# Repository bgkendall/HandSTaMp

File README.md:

# ~~HandSTaMp~~ HandCHime

## Bill of Materials

| Reference | Silkscreen | Part                        | Footprint | Purpose                                        |
|-----------|------------|-----------------------------|-----------|------------------------------------------------|
| C1        | µ          | 4.7µF ceramic capacitor     | 0603      | Bulk decoupling capacitor for U1               |
| C2        | n          | 100nF ceramic capacitor     | 0603      | Decoupling capacitor for U1                    |
| D1        | D1         | PMEG2010EA Schottky diode   | SOD-323   | Reverse current protection                     |
| D2, D3    | D2, D3     | 2 × 1N4148 diodes           | SOD-123   | Matrix diodes for SW1/SW2                      |
| F1        | F          | 500mA fuse                  | 0603      | Current overload protection                    |
| J1        | J1         | HRO TYPE-C-31-M-12 USB port |           | For the pluggings in of USB cables             |
| R1, R2    | 1, 2       | 2 × 5.1kΩ resistors         | 0603      | USB power negotiation (Rd) resistors           |
| R3        | 3          | 5.1kΩ resistor              | 0603      | Boot circuit resistor                          |
| S1, S2    | *None*     | 2 × MX-compatible switches  | MX plate¹ | Keys for row 0, columns 0/1; mountings for PCB |
| S3        | *None*     | B3U-1000P                   |           | Boot switch                                    |
| U1        | *None*²    | CH32X035G8U6                | WQFN-28   | ~~Braaaains!~~ Microcontroller                 |
| U2        | U2         | PRTR5V0U2X                  | SOT-143   | ESD protection                                 |

##### Notes

 1. Three-pin “plate-mount” switches can be used as-is. To use five-pin “PCB-mount” switches,
    one of the plastic alignment “pins” must be removed from opposite sides of each switch.
 2. U1 is positioned in the ~4×4mm area in the lower centre of the PCB.

## Debug Interface

The Serial Debug Interface (SDI) pins are assigned as follows:

 1. **S**quare Pin — **S**WDIO
 2. **C**ircular Pin — SW**C**LK

These pins are intended to be small enough to friction fit debug probe wires.
The pins can alternatively be used as the following extra GPIO pins:

 1. Square Pin — PC18
 2. Circular Pin — PC19

Note that these pins are underneath a switch and can only be soldered from the bottom.
Wires should be trimmed as close to the board as possible.

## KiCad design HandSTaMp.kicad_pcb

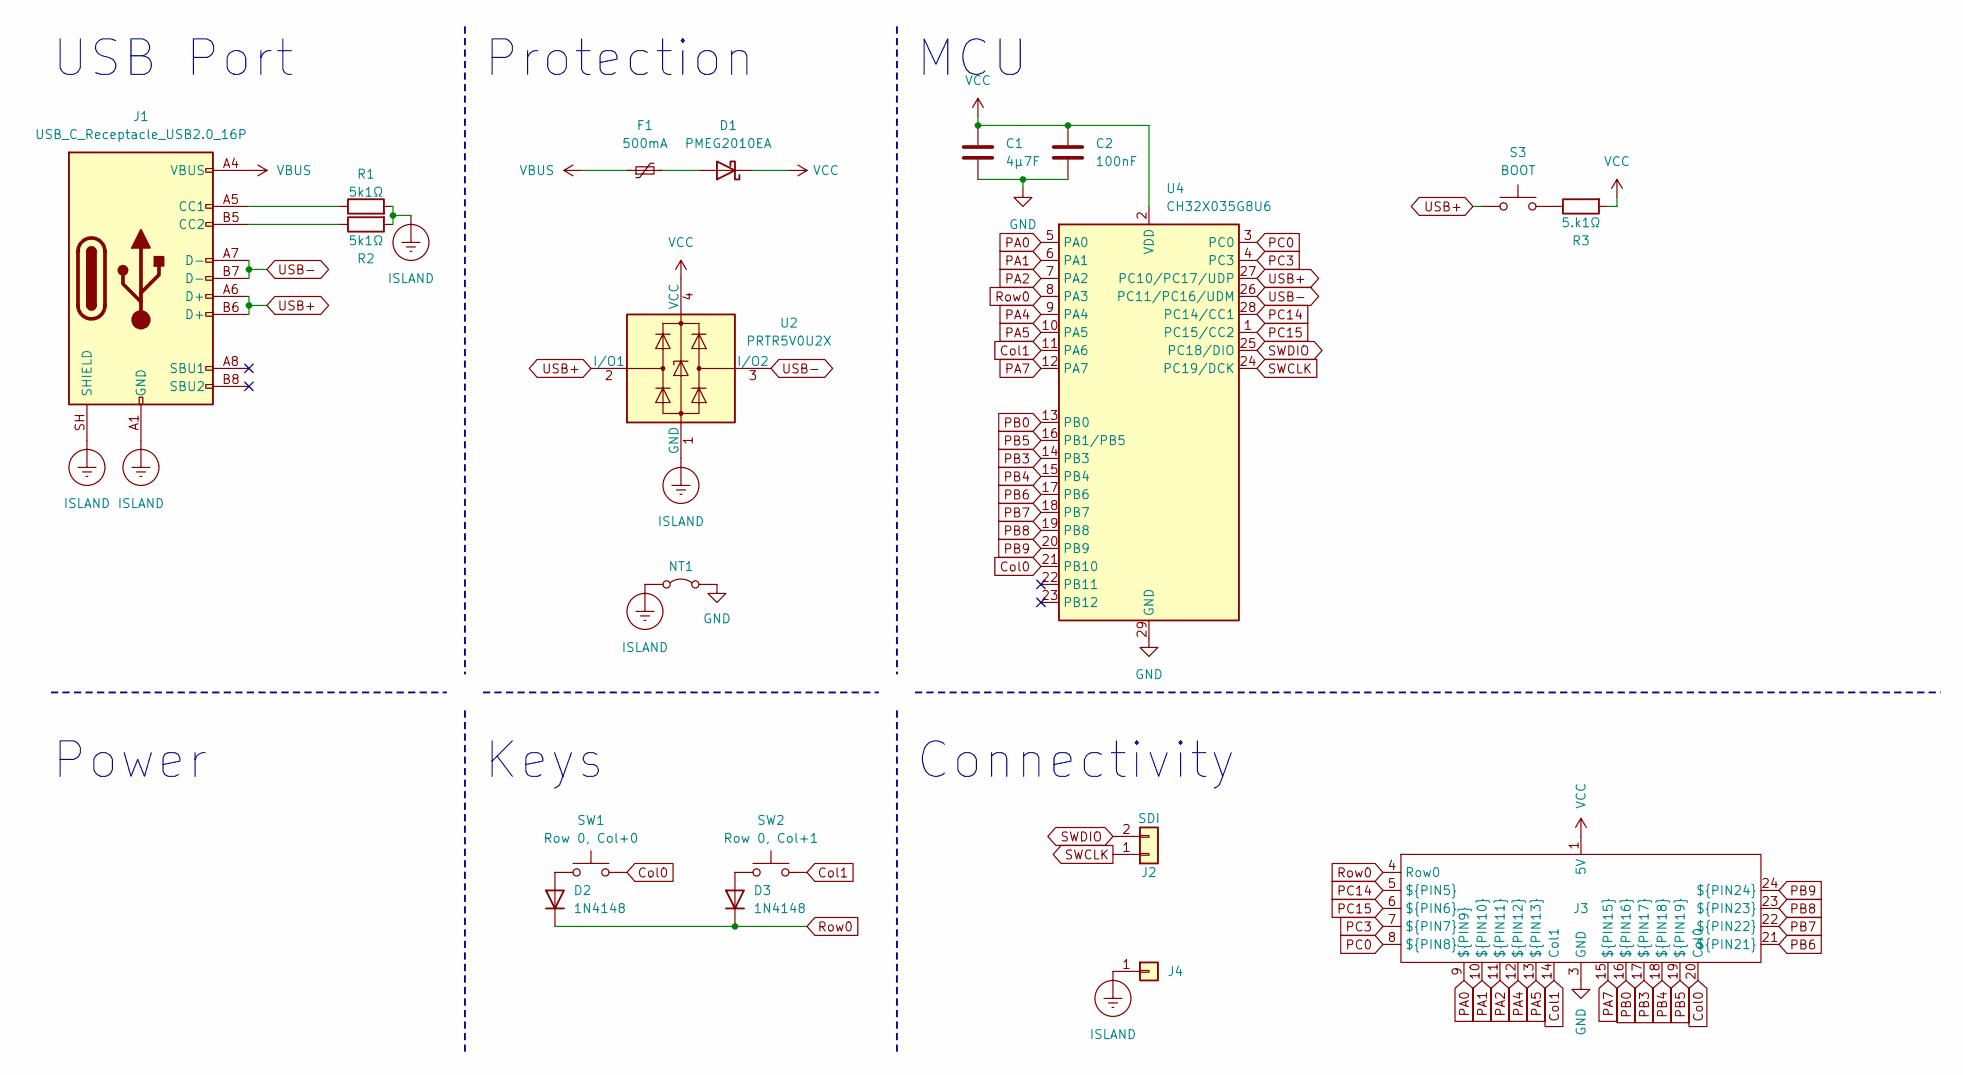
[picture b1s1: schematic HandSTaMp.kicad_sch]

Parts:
C1: 4µ7F; C_0603_1608Metric; MPN CL10A475KO8NNNC; DigiKey 1276-1784-1
C2: 100nF; C_0603_1608Metric; MPN CL10B104KO8NNNC; DigiKey 1276-1005-1
D1: PMEG2010EA; D_SOD-323; MPN PMEG2010EA,115; LCSC C193668
D2, D3: 1N4148; D_SOD-123; MPN 1N4148W; DigiKey 1N4148WQ-7-FDI
F1: 500mA; Fuse_0603_1608Metric; MPN MF-FSMF050X-2; LCSC C210357
J1: USB_C_Receptacle_USB2.0_16P; USB_C_Receptacle_HRO_TYPE-C-31-M-12; MPN TYPE-C-31-M-12; DigiKey 2223-UJ20-C-H-G-SMT-1A-P16 (untested; m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
J2: SDI; SWD
J3: Pins; HandSTaMp
J4: ⏚; SolderWire_1x01_D1mm_OD1.7mm
NT1: Mounting Hole/Isolated Ground Jumper; NetTie-2_SMD_Pad0.5mm
R1, R2: 5k1Ω; R_0603_1608Metric; MPN 0603WAF5101T5E/RC0603FR-075K1L; LCSC C23186
R3: 5.k1Ω; R_0603_1608Metric; MPN 0603WAF3300T5E/RC0603FR-07330RL; LCSC C23138
S3: BOOT; SW_SPST_B3U-1000P; MPN B3U-1000P; LCSC C231329
SW1: Row 0, Col+0; SW_MX_1u_1pinL
SW2: Row 0, Col+1; SW_MX_1u_1pinR
U2: PRTR5V0U2X; SOT-143; MPN PRTR5V0U2X,215; LCSC C12333
U4: CH32X035G8U6; WQFN-28-1EP_4x4mm_P0.4mm_EP2.7x2.7mm

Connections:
Col0: J3.20 (Col0), SW1.1, U4.21 (PB10)
Col1: J3.14 (Col1), SW2.1, U4.11 (PA6)
GND: C1.2, C2.2, J3.3 (GND), NT1.2 (B), U4.29 (GND)
ISLAND: J1.A1 (GND), J1.A12 (GND), J1.B1 (GND), J1.B12 (GND), J1.SH (SHIELD), J4.1 (Pin_1_1), NT1.1 (A), R1.2, R2.2, U2.1 (GND)
unnamed: D1.2 (A), F1.2
unnamed: D2.2 (A), SW1.2
unnamed: D3.2 (A), SW2.2
unnamed: J1.A5 (CC1), R1.1
unnamed: J1.B5 (CC2), R2.1
unnamed: R3.1, S3.2
PA0: J3.9 (${PIN9}), U4.5 (PA0)
PA1: J3.10 (${PIN10}), U4.6 (PA1)
PA2: J3.11 (${PIN11}), U4.7 (PA2)
PA4: J3.12 (${PIN12}), U4.9 (PA4)
PA5: J3.13 (${PIN13}), U4.10 (PA5)
PA7: J3.15 (${PIN15}), U4.12 (PA7)
PB0: J3.16 (${PIN16}), U4.13 (PB0)
PB3: J3.17 (${PIN17}), U4.14 (PB3)
PB4: J3.18 (${PIN18}), U4.15 (PB4)
PB5: J3.19 (${PIN19}), U4.16 (PB1/PB5)
PB6: J3.21 (${PIN21}), U4.17 (PB6)
PB7: J3.22 (${PIN22}), U4.18 (PB7)
PB8: J3.23 (${PIN23}), U4.19 (PB8)
PB9: J3.24 (${PIN24}), U4.20 (PB9)
PC0: J3.8 (${PIN8}), U4.3 (PC0)
PC3: J3.7 (${PIN7}), U4.4 (PC3)
PC14: J3.5 (${PIN5}), U4.28 (PC14/CC1)
PC15: J3.6 (${PIN6}), U4.1 (PC15/CC2)
Row0: D2.1 (K), D3.1 (K), J3.4 (Row0), U4.8 (PA3)
SWCLK: J2.1, U4.24 (PC19/DCK)
SWDIO: J2.2, U4.25 (PC18/DIO)
USB+: J1.A6 (D+), J1.B6 (D+), S3.1, U2.2 (I/O1), U4.27 (PC10/PC17/UDP)
USB-: J1.A7 (D-), J1.B7 (D-), U2.3 (I/O2), U4.26 (PC11/PC16/UDM)
VBUS: F1.1, J1.A4 (VBUS), J1.A9 (VBUS), J1.B4 (VBUS), J1.B9 (VBUS)
VCC: C1.1, C2.1, D1.1 (K), J3.1 (5V), R3.2, U2.4 (VCC), U4.2 (VDD)

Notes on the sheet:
Keys
MCU
Connectivity
Protection
Power
USB Port

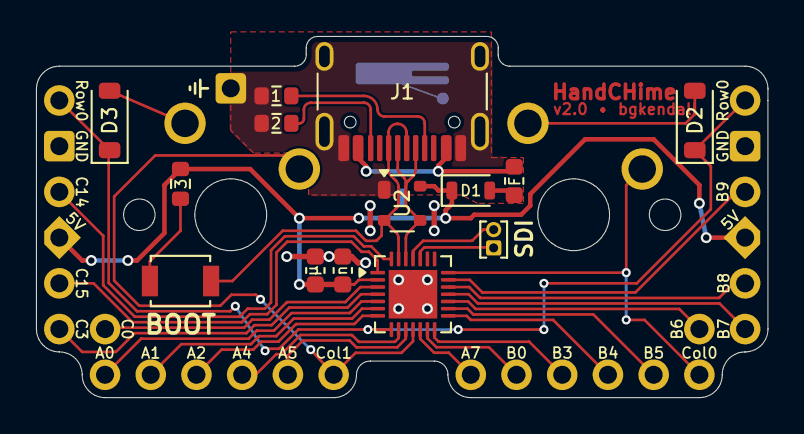
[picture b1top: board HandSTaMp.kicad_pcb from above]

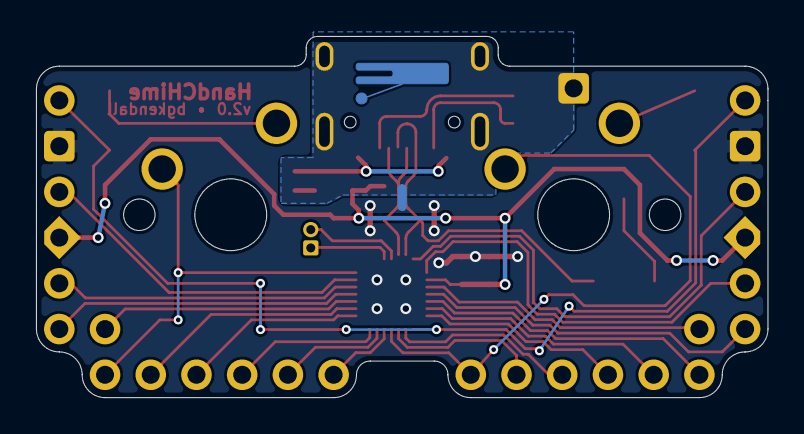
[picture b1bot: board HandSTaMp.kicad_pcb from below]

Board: 2 copper layers, 40.6 x 20.1 mm, 19 parts (3 on the bottom side), 35 nets.

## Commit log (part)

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2026-04-14 Fix README notes
2026-04-14 Tweak routing, especially R1 and C0
2026-04-14 Update constraints and fix various DRC errors
    The logo was getting a “copper slither” warning on the logo, so the handle and base shapes have been merged into one shape.
    The SWD pins have been spaced out a little.
2026-04-24 Refine logo
2026-04-24 Rework LDO area
2026-04-24 Swap column pins to edge of group
2026-04-24 Move version/author label away from D2 silkscreen
2026-04-24 Minor tweaks
2026-04-25 Add LSCC, DigiKey and manufacturer’s part numbers
    BOM could be optimised to substitute some passive components with equivalent “Basic” parts if using JLC assembly.
2026-04-25 Move extra pin to short side
    This better avoids the switch as the left and right sides taper in a bit compared to the top and bottom sides, which are more straight.
2026-04-25 Add pad for PC15 access
2026-04-25 Move pad GPIO to THT connection
    * PC15 pad removed
    * Col1 switched to PC15
    * GND pin near right corner switched to GPIO
    * Bottom right pin assignments shuffled over one
2026-04-25 Update schematic presentation, check ERC and DRC
    Also, fix slight misalignment of external pins on PCB.
2026-04-27 Move items missing in previous change
2026-04-27 Fix erroneously bold text
2026-05-19 Add access to PF2-NRST
